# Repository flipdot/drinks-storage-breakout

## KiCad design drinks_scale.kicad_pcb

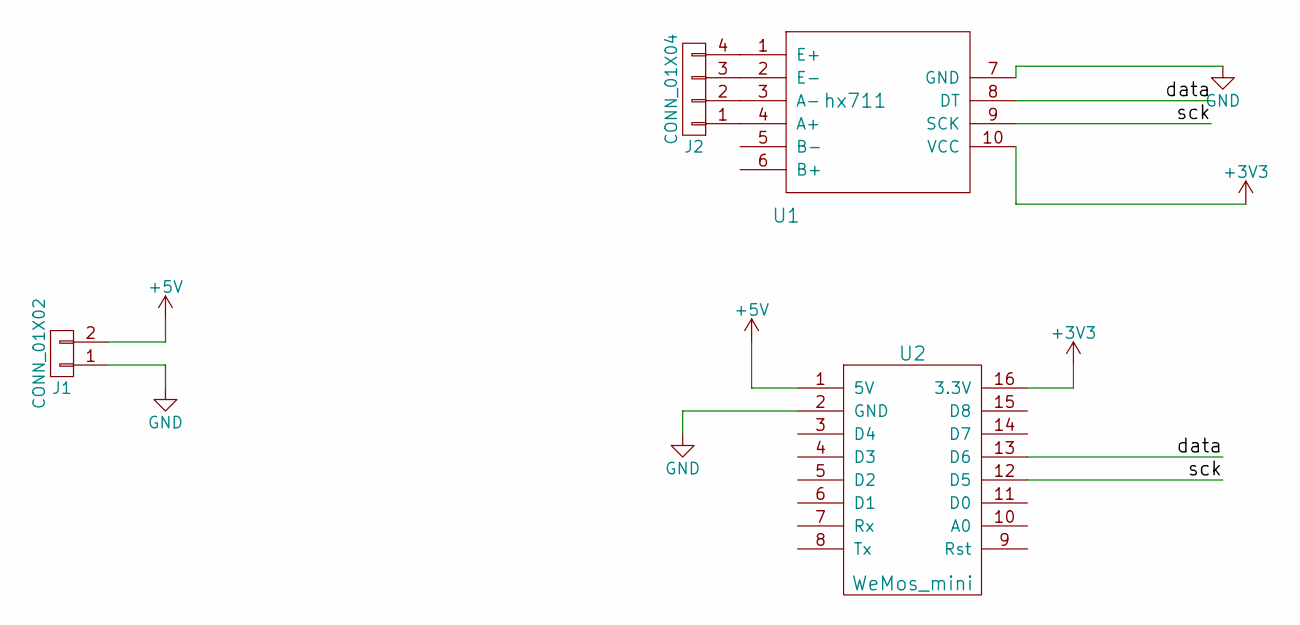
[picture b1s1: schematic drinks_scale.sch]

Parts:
J1: CONN_01X02; Pin_Header_Angled_1x02_Pitch1.00mm
J2: CONN_01X04; Pin_Header_Angled_1x04_Pitch1.00mm
U1: hx711
U2: WeMos_mini; D1_mini_board

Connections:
+3V3: U1.10 (VCC), U2.16 (3.3V)
+5V: J1.2, U2.1 (5V)
/data: U1.8 (DT), U2.13 (D6)
/sck: U1.9 (SCK), U2.12 (D5)
GND: J1.1, U1.7 (GND), U2.2 (GND)
unnamed: J2.1, U1.4 (A+)
unnamed: J2.2, U1.3 (A-)
unnamed: J2.3, U1.2 (E-)
unnamed: J2.4, U1.1 (E+)

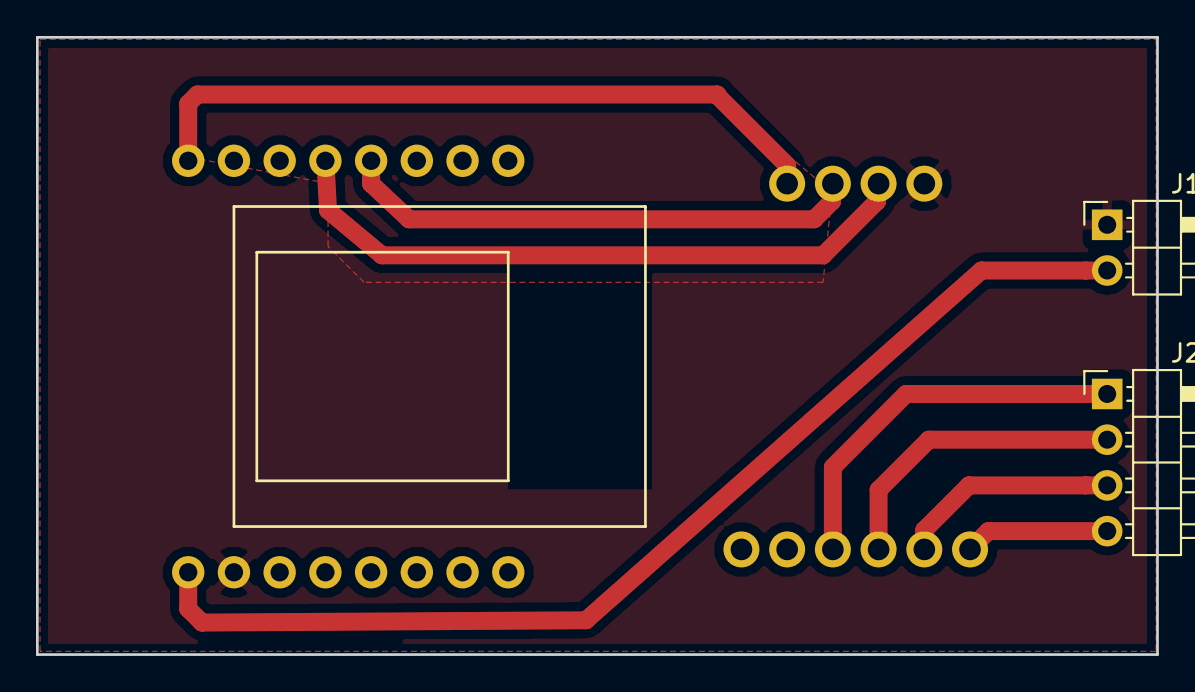
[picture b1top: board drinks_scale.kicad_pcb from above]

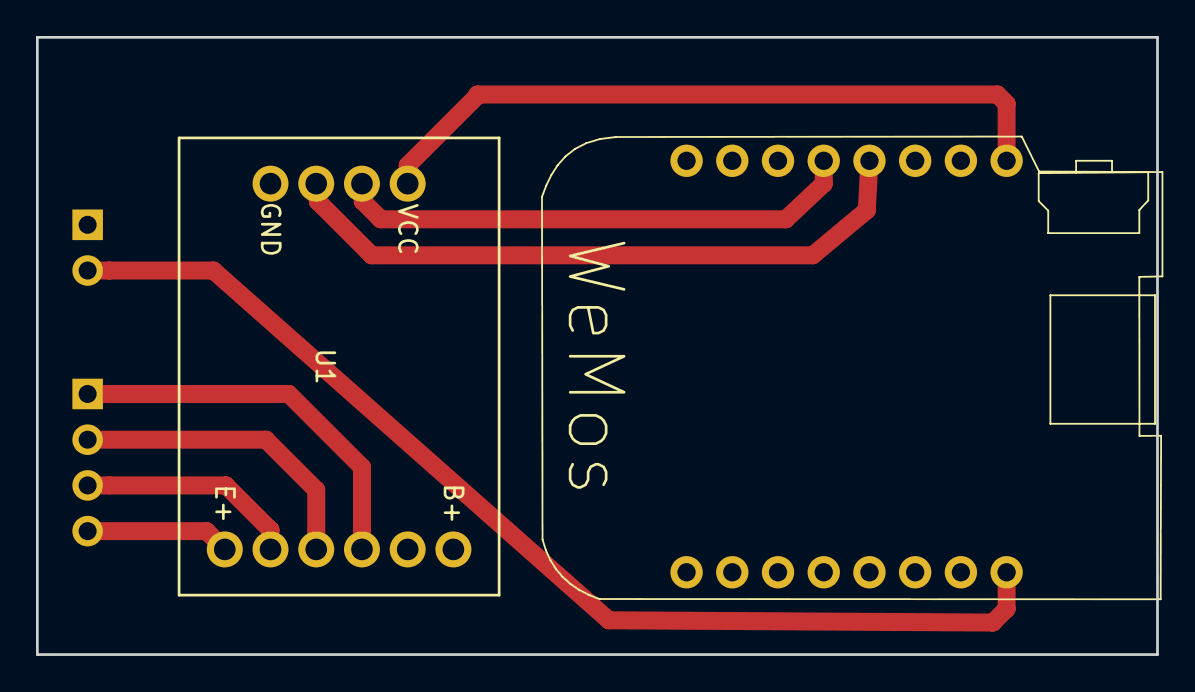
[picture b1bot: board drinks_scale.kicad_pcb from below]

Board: 2 copper layers, 62.2 x 34.3 mm, 4 parts (2 on the bottom side), 9 nets.

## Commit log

2017-09-18 Add preliminary board and stuff
2017-09-18 Add .gitignore
2017-09-18 update gcode files
2017-09-18 add 3mm cutout
2017-10-13 Fix drill size
2017-10-13 Add GND plane
2017-10-13 Update gbr files
2017-10-17 Add etch templates
